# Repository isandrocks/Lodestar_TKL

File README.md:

# Lodestar_TKL
 Custom TKL keyboard. Trying to make it as compacts as possible and still be compatible with a ANSI layout.

## still very much WIP

Here is a render of where im at!

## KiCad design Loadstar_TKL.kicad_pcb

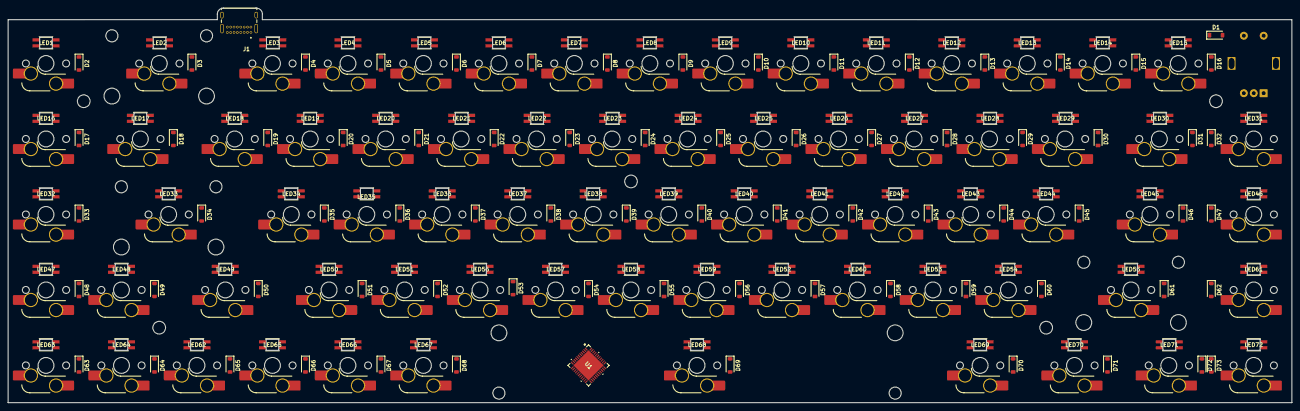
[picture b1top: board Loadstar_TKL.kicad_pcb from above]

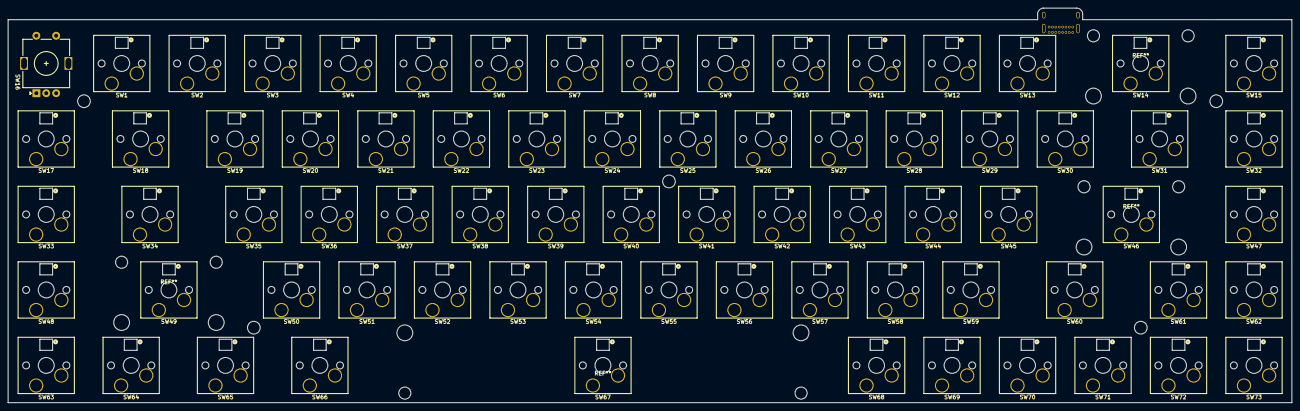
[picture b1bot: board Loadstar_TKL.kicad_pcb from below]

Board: 2 copper layers, 324.0 x 99.6 mm, 220 parts (73 on the bottom side), 167 nets, no tracks yet.

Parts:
D1, D2, D3, D4, D5, D6, D7, D8, D9, D10, D11, D12, D13, D14, D15, D16, D17, D18, D19, D20, D21, D22, D23, D24, D25, D26, D27, D28, D29, D30, D31, D32, D33, D34, D35, D36, D37, D38, D39, D40, D41, D42, D43, D44, D45, D46, D47, D48, D49, D50, D51, D52, D53, D54, D55, D56, D57, D58, D59, D60, D61, D62, D63, D64, D65, D66, D67, D68, D69, D70, D71, D72, D73: 1N4007; D_SOD-123
J1: USB-C; USB4085-GF-A_REVB_GCT_USB4085-GF-A_REVB
LED1, LED2, LED3, LED4, LED5, LED6, LED7, LED8, LED9, LED10, LED11, LED12, LED13, LED14, LED15, LED16, LED17, LED18, LED19, LED20, LED21, LED22, LED23, LED24, LED25, LED26, LED27, LED28, LED29, LED30, LED31, LED32, LED33, LED34, LED35, LED36, LED37, LED38, LED39, LED40, LED41, LED42, LED43, LED44, LED45, LED46, LED47, LED48, LED49, LED50, LED51, LED52, LED53, LED54, LED55, LED56, LED57, LED58, LED59, LED60, LED61, LED62, LED63, LED64, LED65, LED66, LED67, LED68, LED69, LED70, LED71, LED72: 4960; 4960_ADA
SW1, SW2, SW3, SW4, SW5, SW6, SW7, SW8, SW9, SW10, SW11, SW12, SW13, SW15, SW17, SW19, SW20, SW21, SW22, SW23, SW24, SW25, SW26, SW27, SW28, SW29, SW30, SW32, SW33, SW35, SW36, SW37, SW38, SW39, SW40, SW41, SW42, SW43, SW44, SW45, SW47, SW48, SW50, SW51, SW52, SW53, SW54, SW55, SW56, SW57, SW58, SW59, SW61, SW62, SW63, SW68, SW69, SW70, SW71, SW72, SW73: SW_Push; SW_Hotswap_Kailh_MX_Plated_1.00u
SW14: SW_Push; SW_Hotswap_Kailh_MX_Plated_2.00u
SW16: RotaryEncoder_Switch; RotaryEncoder_Alps_EC11E-Switch_Vertical_H20mm
SW18, SW31: SW_Push; SW_Hotswap_Kailh_MX_Plated_1.50u
SW34, SW60: SW_Push; SW_Hotswap_Kailh_MX_Plated_1.75u
SW46, SW49: SW_Push; SW_Hotswap_Kailh_MX_Plated_2.25u
SW64, SW65, SW66: SW_Push; SW_Hotswap_Kailh_MX_Plated_1.25u
SW67: SW_Push; SW_Hotswap_Kailh_MX_Plated_6.25u
U1: ATMEGA32U4RC-MUR; 44PW_ATM

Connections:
+5V: LED1.1 (VDD), LED2.1 (VDD), LED3.1 (VDD), LED4.1 (VDD), LED5.1 (VDD), LED6.1 (VDD), LED7.1 (VDD), LED8.1 (VDD), LED9.1 (VDD), LED10.1 (VDD), LED11.1 (VDD), LED12.1 (VDD), LED13.1 (VDD), LED14.1 (VDD), LED15.1 (VDD), LED17.1 (VDD), LED18.1 (VDD), LED19.1 (VDD), LED20.1 (VDD), LED21.1 (VDD), LED22.1 (VDD), LED23.1 (VDD), LED24.1 (VDD), LED25.1 (VDD), LED26.1 (VDD), LED27.1 (VDD), LED28.1 (VDD), LED29.1 (VDD), LED30.1 (VDD), LED31.1 (VDD), LED32.1 (VDD), LED33.1 (VDD), LED34.1 (VDD), LED35.1 (VDD), LED36.1 (VDD), LED37.1 (VDD), LED38.1 (VDD), LED39.1 (VDD), LED40.1 (VDD), LED41.1 (VDD), LED42.1 (VDD), LED43.1 (VDD), LED44.1 (VDD), LED45.1 (VDD), LED46.1 (VDD), LED47.1 (VDD), LED48.1 (VDD), LED49.1 (VDD), LED50.1 (VDD), LED51.1 (VDD), LED52.1 (VDD), LED53.1 (VDD), LED54.1 (VDD), LED55.1 (VDD), LED56.1 (VDD), LED57.1 (VDD), LED58.1 (VDD), LED59.1 (VDD), LED60.1 (VDD), LED61.1 (VDD), LED62.1 (VDD), LED63.1 (VDD), LED64.1 (VDD), LED65.1 (VDD), LED66.1 (VDD), LED67.1 (VDD), LED68.1 (VDD), LED69.1 (VDD), LED70.1 (VDD), LED71.1 (VDD), LED72.1 (VDD), U1.14 (VCC), U1.24 (AVCC)
GND: J1.A1 (GND), J1.A12 (GND__1), J1.B1 (GND__2), J1.B12 (GND__3), J1.S1 (SHELL), J1.S2 (SHELL__1), J1.S3 (SHELL__2), J1.S4 (SHELL__3), LED1.3 (GND), LED2.3 (GND), LED3.3 (GND), LED4.3 (GND), LED5.3 (GND), LED6.3 (GND), LED7.3 (GND), LED8.3 (GND), LED9.3 (GND), LED10.3 (GND), LED11.3 (GND), LED12.3 (GND), LED13.3 (GND), LED14.3 (GND), LED15.3 (GND), LED16.3 (GND), LED17.3 (GND), LED18.3 (GND), LED19.3 (GND), LED20.3 (GND), LED21.3 (GND), LED22.3 (GND), LED23.3 (GND), LED24.3 (GND), LED25.3 (GND), LED26.3 (GND), LED27.3 (GND), LED28.3 (GND), LED29.3 (GND), LED30.3 (GND), LED31.3 (GND), LED32.3 (GND), LED33.3 (GND), LED34.3 (GND), LED35.3 (GND), LED36.3 (GND), LED37.3 (GND), LED38.3 (GND), LED39.3 (GND), LED40.3 (GND), LED41.3 (GND), LED42.3 (GND), LED43.3 (GND), LED44.3 (GND), LED45.3 (GND), LED46.3 (GND), LED47.3 (GND), LED48.3 (GND), LED49.3 (GND), LED50.3 (GND), LED51.3 (GND), LED52.3 (GND), LED53.3 (GND), LED54.3 (GND), LED55.3 (GND), LED56.3 (GND), LED57.3 (GND), LED58.3 (GND), LED59.3 (GND), LED60.3 (GND), LED61.3 (GND), LED62.3 (GND), LED63.3 (GND), LED64.3 (GND), LED65.3 (GND), LED66.3 (GND), LED67.3 (GND), LED68.3 (GND), LED69.3 (GND), LED70.3 (GND), LED71.3 (GND), LED72.3 (GND), U1.15 (GND), U1.23 (GND)
unnamed: D16.2 (A), SW1.2
unnamed: D15.2 (A), SW2.2
unnamed: D14.2 (A), SW3.2
unnamed: D13.2 (A), SW4.2
unnamed: D12.2 (A), SW5.2
unnamed: D11.2 (A), SW6.2
unnamed: D10.2 (A), SW7.2
unnamed: D9.2 (A), SW8.2
unnamed: D8.2 (A), SW9.2
unnamed: D7.2 (A), SW10.2
unnamed: D6.2 (A), SW11.2
unnamed: D5.2 (A), SW12.2
unnamed: D4.2 (A), SW13.2
unnamed: D3.2 (A), SW14.2
unnamed: D2.2 (A), SW15.2
unnamed: D33.2 (A), SW47.2
unnamed: D31.2 (A), SW18.2
unnamed: D30.2 (A), SW19.2
unnamed: D29.2 (A), SW20.2
unnamed: D28.2 (A), SW21.2
unnamed: D27.2 (A), SW22.2
unnamed: D26.2 (A), SW23.2
unnamed: D25.2 (A), SW24.2
unnamed: D24.2 (A), SW25.2
unnamed: D23.2 (A), SW26.2
unnamed: D22.2 (A), SW27.2
unnamed: D21.2 (A), SW28.2
unnamed: D20.2 (A), SW29.2
unnamed: D19.2 (A), SW30.2
unnamed: D18.2 (A), SW31.2
unnamed: D17.2 (A), SW32.2
unnamed: D48.2 (A), SW62.2
unnamed: D46.2 (A), SW34.2
unnamed: D45.2 (A), SW35.2
unnamed: D44.2 (A), SW36.2
unnamed: D43.2 (A), SW37.2
unnamed: D42.2 (A), SW38.2
unnamed: D41.2 (A), SW39.2
unnamed: D40.2 (A), SW40.2
unnamed: D39.2 (A), SW41.2
unnamed: D38.2 (A), SW42.2
unnamed: D37.2 (A), SW43.2
unnamed: D36.2 (A), SW44.2
unnamed: D35.2 (A), SW45.2
unnamed: D34.2 (A), SW46.2
unnamed: D61.2 (A), SW49.2
unnamed: D60.2 (A), SW50.2
unnamed: D59.2 (A), SW51.2
unnamed: D58.2 (A), SW52.2
unnamed: D57.2 (A), SW53.2
unnamed: D56.2 (A), SW54.2
unnamed: D55.2 (A), SW55.2
unnamed: D54.2 (A), SW56.2
unnamed: D53.2 (A), SW57.2
unnamed: D52.2 (A), SW58.2
unnamed: D51.2 (A), SW59.2
unnamed: D50.2 (A), SW60.2
unnamed: D49.2 (A), SW61.2
unnamed: D72.2 (A), SW64.2
unnamed: D71.2 (A), SW65.2
unnamed: D70.2 (A), SW66.2
unnamed: D69.2 (A), SW67.2
unnamed: D68.2 (A), SW68.2
unnamed: D67.2 (A), SW69.2
unnamed: D66.2 (A), SW70.2
unnamed: D65.2 (A), SW71.2
unnamed: D64.2 (A), SW72.2
unnamed: D63.2 (A), SW73.2
unnamed: D1.2 (A), SW16.S1
unnamed: D32.2 (A), SW17.2
unnamed: D47.2 (A), SW33.2
unnamed: D62.2 (A), SW48.2
unnamed: D73.2 (A), SW63.2
unnamed: J1.A7 (DN1), J1.B7 (DN2)
unnamed: J1.A6 (DP1), J1.B6 (DP2)
unnamed: J1.A4 (VBUS), J1.A9 (VBUS__1), J1.B4 (VBUS__2), J1.B9 (VBUS__3)
unnamed: LED1.4 (DIN), LED2.2 (DOUT)
unnamed: LED2.4 (DIN), LED3.2 (DOUT)
unnamed: LED3.4 (DIN), LED4.2 (DOUT)
unnamed: LED4.4 (DIN), LED5.2 (DOUT)
unnamed: LED5.4 (DIN), LED6.2 (DOUT)
unnamed: LED6.4 (DIN), LED7.2 (DOUT)
unnamed: LED7.4 (DIN), LED8.2 (DOUT)
unnamed: LED8.4 (DIN), LED9.2 (DOUT)
unnamed: LED10.4 (DIN), LED11.2 (DOUT)
unnamed: LED9.4 (DIN), LED10.2 (DOUT)
unnamed: LED11.4 (DIN), LED12.2 (DOUT)
unnamed: LED12.4 (DIN), LED13.2 (DOUT)
unnamed: LED13.4 (DIN), LED14.2 (DOUT)
unnamed: LED14.4 (DIN), LED15.2 (DOUT)
unnamed: LED17.4 (DIN), LED18.2 (DOUT)
unnamed: LED16.4 (DIN), LED17.2 (DOUT)
unnamed: LED18.4 (DIN), LED19.2 (DOUT)
unnamed: LED19.4 (DIN), LED20.2 (DOUT)
unnamed: LED20.4 (DIN), LED21.2 (DOUT)
unnamed: LED21.4 (DIN), LED22.2 (DOUT)
unnamed: LED22.4 (DIN), LED23.2 (DOUT)
unnamed: LED23.4 (DIN), LED24.2 (DOUT)
unnamed: LED24.4 (DIN), LED25.2 (DOUT)
unnamed: LED25.4 (DIN), LED26.2 (DOUT)
unnamed: LED26.4 (DIN), LED27.2 (DOUT)
unnamed: LED27.4 (DIN), LED28.2 (DOUT)
unnamed: LED28.4 (DIN), LED29.2 (DOUT)
unnamed: LED29.4 (DIN), LED30.2 (DOUT)
unnamed: LED30.4 (DIN), LED31.2 (DOUT)
unnamed: LED33.4 (DIN), LED34.2 (DOUT)
unnamed: LED32.4 (DIN), LED33.2 (DOUT)
unnamed: LED35.4 (DIN), LED36.2 (DOUT)
unnamed: LED34.4 (DIN), LED35.2 (DOUT)
unnamed: LED36.4 (DIN), LED37.2 (DOUT)
unnamed: LED37.4 (DIN), LED38.2 (DOUT)
unnamed: LED38.4 (DIN), LED39.2 (DOUT)
unnamed: LED39.4 (DIN), LED40.2 (DOUT)
unnamed: LED40.4 (DIN), LED41.2 (DOUT)
unnamed: LED41.4 (DIN), LED42.2 (DOUT)
unnamed: LED42.4 (DIN), LED43.2 (DOUT)
unnamed: LED43.4 (DIN), LED44.2 (DOUT)
unnamed: LED44.4 (DIN), LED45.2 (DOUT)
unnamed: LED45.4 (DIN), LED46.2 (DOUT)
unnamed: LED48.4 (DIN), LED49.2 (DOUT)
unnamed: LED47.4 (DIN), LED48.2 (DOUT)
unnamed: LED49.4 (DIN), LED50.2 (DOUT)
unnamed: LED50.4 (DIN), LED51.2 (DOUT)
unnamed: LED51.4 (DIN), LED56.2 (DOUT)
unnamed: LED56.4 (DIN), LED57.2 (DOUT)
unnamed: LED57.4 (DIN), LED58.2 (DOUT)
unnamed: LED58.4 (DIN), LED59.2 (DOUT)
unnamed: LED52.2 (DOUT), LED59.4 (DIN)
unnamed: LED52.4 (DIN), LED60.2 (DOUT)
unnamed: LED53.2 (DOUT), LED60.4 (DIN)
unnamed: LED53.4 (DIN), LED54.2 (DOUT)
unnamed: LED54.4 (DIN), LED55.2 (DOUT)
unnamed: LED55.4 (DIN), LED61.2 (DOUT)
unnamed: LED62.2 (DOUT), LED64.4 (DIN)
unnamed: LED63.4 (DIN), LED64.2 (DOUT)
unnamed: LED62.4 (DIN), LED65.2 (DOUT)
unnamed: LED65.4 (DIN), LED66.2 (DOUT)
unnamed: LED66.4 (DIN), LED67.2 (DOUT)
unnamed: LED67.4 (DIN), LED68.2 (DOUT)
unnamed: LED68.4 (DIN), LED69.2 (DOUT)
unnamed: LED69.4 (DIN), LED70.2 (DOUT)
unnamed: LED70.4 (DIN), LED71.2 (DOUT)
unnamed: LED71.4 (DIN), LED72.2 (DOUT)
col0: SW16.S2, SW17.1, SW33.1, SW48.1, SW63.1
col2: SW1.1, SW18.1, SW34.1, SW49.1, SW64.1
col3: SW2.1, SW19.1, SW35.1, SW65.1
col4: SW3.1, SW20.1, SW36.1, SW50.1, SW66.1
col5: SW4.1, SW21.1, SW37.1, SW51.1
col6: SW5.1, SW22.1, SW38.1, SW52.1
col7: SW6.1, SW23.1, SW39.1, SW53.1
col8: SW7.1, SW24.1, SW40.1, SW54.1, SW67.1
col9: SW8.1, SW25.1, SW41.1, SW55.1
col10: SW9.1, SW26.1, SW42.1, SW56.1
col11: SW10.1, SW27.1, SW43.1, SW57.1
col12: SW11.1, SW28.1, SW44.1, SW58.1, SW68.1
col13: SW12.1, SW29.1, SW45.1, SW59.1, SW69.1
col14: SW13.1, SW30.1, SW70.1
col15: SW14.1, SW31.1, SW46.1, SW60.1, SW71.1
col16: SW61.1, SW72.1
col17: SW15.1, SW32.1, SW47.1, SW62.1, SW73.1
row0: D1.1 (K), D2.1 (K), D3.1 (K), D4.1 (K), D5.1 (K), D6.1 (K), D7.1 (K), D8.1 (K), D9.1 (K), D10.1 (K), D11.1 (K), D12.1 (K), D13.1 (K), D14.1 (K), D15.1 (K), D16.1 (K)
row1: D17.1 (K), D18.1 (K), D19.1 (K), D20.1 (K), D21.1 (K), D22.1 (K), D23.1 (K), D24.1 (K), D25.1 (K), D26.1 (K), D27.1 (K), D28.1 (K), D29.1 (K), D30.1 (K), D31.1 (K), D32.1 (K)
row2: D33.1 (K), D34.1 (K), D35.1 (K), D36.1 (K), D37.1 (K), D38.1 (K), D39.1 (K), D40.1 (K), D41.1 (K), D42.1 (K), D43.1 (K), D44.1 (K), D45.1 (K), D46.1 (K), D47.1 (K)
row3: D48.1 (K), D49.1 (K), D50.1 (K), D51.1 (K), D52.1 (K), D53.1 (K), D54.1 (K), D55.1 (K), D56.1 (K), D57.1 (K), D58.1 (K), D59.1 (K), D60.1 (K), D61.1 (K), D62.1 (K)
row4: D63.1 (K), D64.1 (K), D65.1 (K), D66.1 (K), D67.1 (K), D68.1 (K), D69.1 (K), D70.1 (K), D71.1 (K), D72.1 (K), D73.1 (K)

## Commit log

2024-02-10 key layout complete
2024-02-16 progress update
2024-02-20 wip update
2024-02-29 general updates
2024-03-15 wireing update
2024-05-03 prototype finished
